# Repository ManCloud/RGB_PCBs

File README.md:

# RGB-PCBs
Console video cable connector PCBs

The user [Arcade TV](https://circuit-board.de/forum/index.php/User/1861-ArcadeTV/) in the Circuit-Board community once created the first ["VSAB"s -> Vertical SCART Adaper Boards](https://circuit-board.de/forum/index.php/Thread/14997-VSAB-Vertical-Scart-Adapter-Boards-outdated/).

In 2020 he found a Post by viletim mentioning, that it's better to have the additional components on console end of the cable instead of the TV end.
So i decided to invent a PCB which would make it easier to solder these cables inspired by the VSABs but for the console end.

As the VSAB boards then no longer needed any components (alsmost) i changed them a bit as well.
 
Links to OSHPark
* Multi-Out:
  * Nintendo: 	https://oshpark.com/shared_projects/a01xTNnj
  * Sony: 		https://oshpark.com/shared_projects/g5j2vvd2
* VSAB
  * Plain: https://oshpark.com/shared_projects/fAsvh5mm
  * 75P: https://oshpark.com/shared_projects/UipCRrXt

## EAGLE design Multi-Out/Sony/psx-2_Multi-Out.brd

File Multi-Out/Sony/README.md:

# Sony
https://oshpark.com/shared_projects/g5j2vvd2

## Purpose
These PCBs can be used to create cables that can be used on Playstation 1,2 and 3.

If you want to use the N64 make sure you have an RGB-modded one or you can only use CV (Composite-Video), as these boards do not support S-Video.

## Configurations
The configuraions all claim to be used with a direct wiring (e.g. with the VSAB-Plain)

### Playstation 1
| Connection | Configuration |
| :-------------: | :-----: |
| SJ2 | either Luma or CV |
| SJ4/C1| 220uF |
| SJ3/C2| 220uF |
| SJ1/C3| 220uF |

### Playstation 2 (3)
| Connection | Configuration |
| :-------------: | :-----: |
| SJ1/C4 | either Luma or CV |
| SJ3/C1| bridged |
| SJ4/C2| bridged |
| SJ5/C3| bridged |

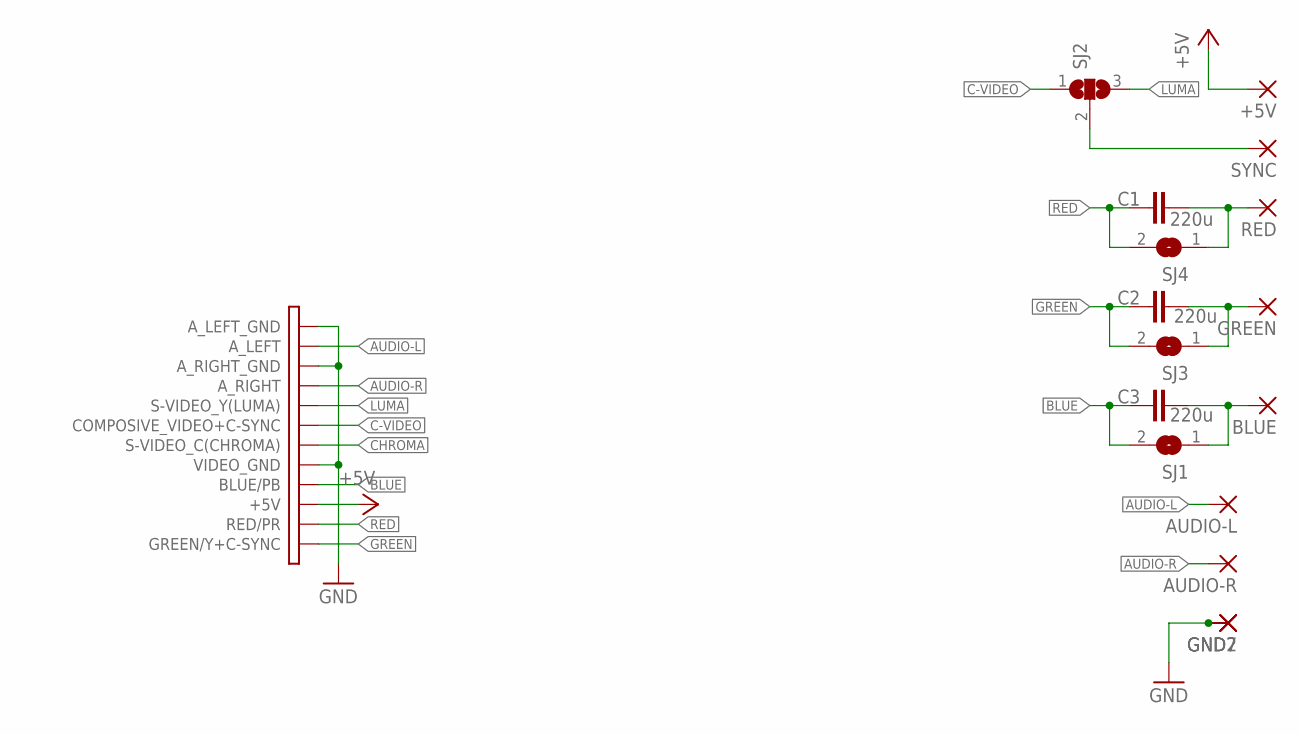
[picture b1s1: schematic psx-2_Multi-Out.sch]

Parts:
+5V: WIREPADSMD1,27-254; SMD1,27-2,54
AUDIO-L: WIREPADSMD1,27-254; SMD1,27-2,54
AUDIO-R: WIREPADSMD1,27-254; SMD1,27-2,54
BLUE: WIREPADSMD1,27-254; SMD1,27-2,54
C1, C2, C3: 220u; C1206
GND2, GND7: WIREPADSMD1,27-254; SMD1,27-2,54
GREEN: WIREPADSMD1,27-254; SMD1,27-2,54
J1: PS/2_MULTI-AV
RED: WIREPADSMD1,27-254; SMD1,27-2,54
SJ1, SJ3, SJ4: SJ
SJ2: SJ2W; SJ_2
SYNC: WIREPADSMD1,27-254; SMD1,27-2,54

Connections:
+5V: +5V.1, J1.+5V
AUDIO-L: AUDIO-L.1, J1.A_LEFT
AUDIO-R: AUDIO-R.1, J1.A_RIGHT
BLUE: C3.1, J1.BLUE/PB, SJ1.2
BLUE'': BLUE.1, C3.2, SJ1.1
C-VIDEO: J1.COMPOSITE_VIDEO+C-S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 (COMPOSIVE_VIDEO+C-SYNC), SJ2.1
CHROMA: J1.S-VIDEO_C(CHROMA)
GND: GND2.1, GND7.1, J1.A_LEFT_GND, J1.A_RIGHT_GND, J1.VIDEO_GND
GREEN: C2.1, J1.GREEN/Y+C-SYNC, SJ3.2
GREEN'': C2.2, GREEN.1, SJ3.1
LUMA: J1.S-VIDEO_Y(LUMA), SJ2.3
RED: C1.1, J1.RED/PR, SJ4.2
RED'': C1.2, RED.1, SJ4.1
SYNC: SJ2.2, SYNC.1

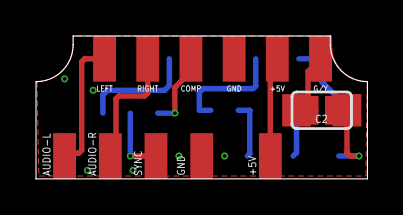
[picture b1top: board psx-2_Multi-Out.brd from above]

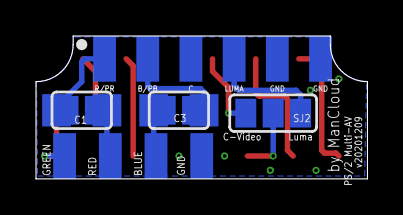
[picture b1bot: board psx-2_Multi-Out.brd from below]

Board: 2 copper layers, 18.4 x 7.9 mm, 17 parts (9 on the bottom side), 13 nets.

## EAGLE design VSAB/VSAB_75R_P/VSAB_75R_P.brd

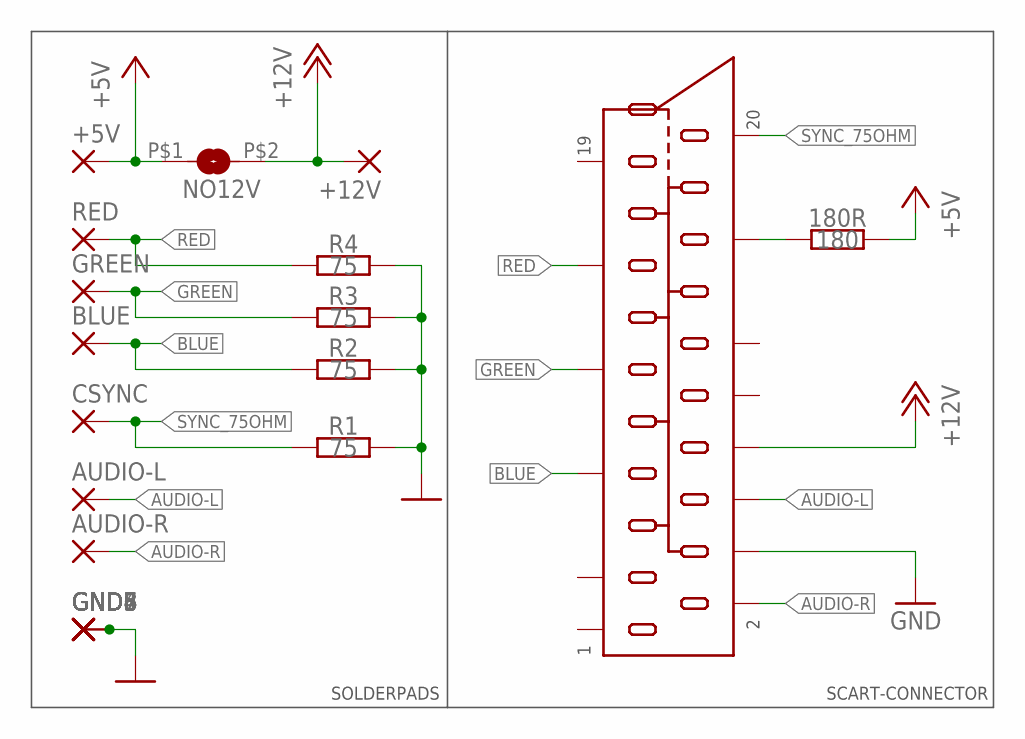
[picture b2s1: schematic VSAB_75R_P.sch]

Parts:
180R: 180; R0805
+5V, +12V: WIREPADSMD5-1,8; 5-1,8
AUDIO-L: WIREPADSMD5-1,8; 5-1,8
AUDIO-R: WIREPADSMD5-1,8; 5-1,8
BLUE: WIREPADSMD5-1,8; 5-1,8
CSYNC: WIREPADSMD5-1,8; 5-1,8
GND, GND3, GND4, GND5, GND6, GND7, GND8: WIREPADSMD5-1,8; 5-1,8
GREEN: WIREPADSMD5-1,8; 5-1,8
NO12V: MY_JUMPER; MYJUMP
R1, R2, R3, R4: 75; R0805
RED: WIREPADSMD5-1,8; 5-1,8
U$2: SCART_PLUG; SCART

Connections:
+5V: 180R.1, +5V.1, NO12V.P$1 (1)
+5V': 180R.2, U$2.16 (AV/RGB_SW)
+12V: +12V.1, NO12V.P$2 (2), U$2.8 (TV/AV_SW)
AUDIO-L: AUDIO-L.1, U$2.6 (AUDIO_IN_L)
AUDIO-R: AUDIO-R.1, U$2.2 (AUDIO_IN_R)
BLUE: BLUE.1, R2.2, U$2.7 (RGB_BLUE/YUV_V/PB)
GND: GND.1, GND3.1, GND4.1, GND5.1, GND6.1, GND7.1, GND8.1, R1.1, R2.1, R3.1, R4.1, U$2.4 (GND), U$2.5 (GND), U$2.9 (GND), U$2.13 (GND), U$2.14 (GND), U$2.17 (GND), U$2.18 (GND)
GREEN: GREEN.1, R3.2, U$2.11 (RGB_GREEN/YUV-Y)
RED: R4.2, RED.1, U$2.15 (RGB_RED/YUV-U/PR/CHROMA)
SYNC_75OHM: CSYNC.1, R1.2, U$2.20 (COMP/SYNC/LUMA_IN)

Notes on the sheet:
SOLDERPADS
SCART-CONNECTOR

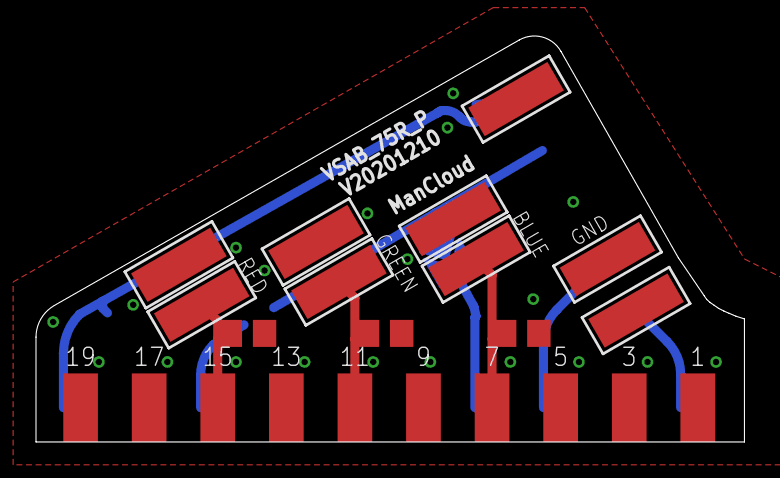
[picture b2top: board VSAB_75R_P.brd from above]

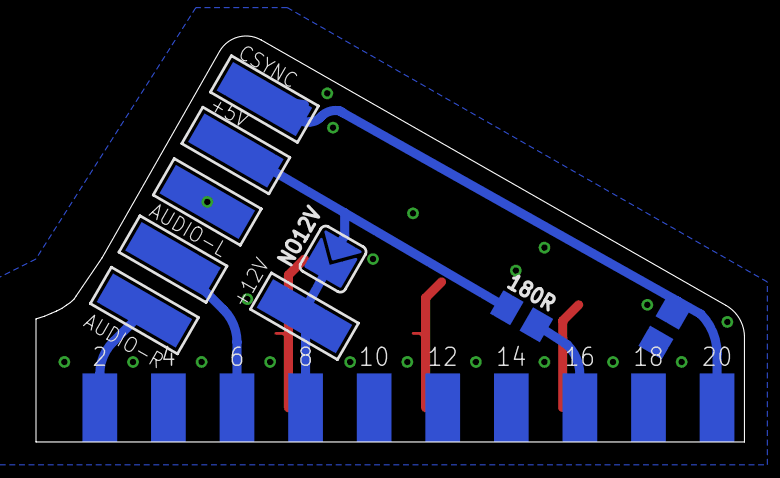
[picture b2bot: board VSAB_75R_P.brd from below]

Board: 2 copper layers, 39.4 x 22.6 mm, 22 parts (9 on the bottom side), 10 nets.

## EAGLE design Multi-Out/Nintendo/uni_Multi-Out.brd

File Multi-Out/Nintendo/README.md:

# Nintendo
https://oshpark.com/shared_projects/a01xTNnj

## Purpose
These PCBs can be used to create cables that can be used on SNES, N64 and GameCube.

If you want to use the N64 make sure you have an RGB-modded one or you can only use CV (Composite-Video), as these boards do not support S-Video.

## Configurations
The configuraions all claim to be used with a direct wiring (e.g. with the VSAB-Plain)

### PAL-SNES
| Connection | Configuration |
| :-------------: | :-----: |
| SJ1/C4 | bridged |
| SJ3/C1| bridged |
| SJ4/C2| bridged |
| SJ5/C3| bridged |
| SJ2| either Luma or CV |
| R1| n.p. |
| R2| 75Ohm |
| R4| 75Ohm |
| R5| 75Ohm |
| R6| 75Ohm |

### NTSC-SNES
| Connection | Configuration |
| :-------------: | :-----: |
| SJ1/C4 | bridged |
| SJ3/C1| 220uF |
| SJ4/C2| 220uF |
| SJ5/C3| 220uF |
| SJ2| either Luma or CV |
| R1| n.p. |
| R2| n.p. |
| R4| n.p. |
| R5| n.p. |
| R6| n.p. |

### PAL-GameCube
| Connection | Configuration |
| :-------------: | :-----: |
| SJ1/C4 | 220uF |
| SJ3/C1| 220uF |
| SJ4/C2| 220uF |
| SJ5/C3| 220uF |
| SJ2| CV |
| R1| n.p. |
| R2| 75Ohm |
| R4| n.p. |
| R5| n.p. |
| R6| n.p. |

### N64
The N64 is different here. It depents on your mod which configuration you need.

E.g.: if you're using [borti4938](https://github.com/borti4938)s [N64Advanced](https://github.com/borti4938/n64rgb/tree/master/advancedRGBmod) Mod, you'd not place any part on the PCB at all:

| Connection | Configuration |
| :-------------: | :-----: |
| SJ1/C4 | bridged |
| SJ3/C1| bridged |
| SJ4/C2| bridged |
| SJ5/C3| bridged |
| SJ2| according to mod |
| R1| n.p. |
| R2| n.p. |
| R4| n.p. |
| R5| n.p. |
| R6| n.p. |

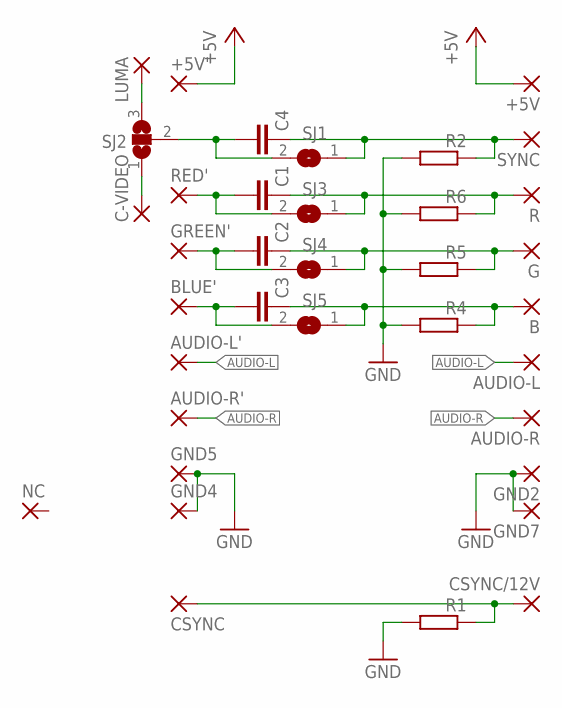
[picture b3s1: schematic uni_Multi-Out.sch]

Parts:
+5V, +5V': WIREPADSMD1,27-254; SMD1,27-2,54
AUDIO-L: WIREPADSMD1,27-254; SMD1,27-2,54
AUDIO-L': WIREPADSMD1,27-254; SMD1,27-2,54
AUDIO-R: WIREPADSMD1,27-254; SMD1,27-2,54
AUDIO-R': WIREPADSMD1,27-254; SMD1,27-2,54
B: WIREPADSMD1,27-254; SMD1,27-2,54
BLUE': WIREPADSMD1,27-254; SMD1,27-2,54
C1, C2, C3, C4: C-EUC1206; C1206
C-VIDEO: WIREPADSMD1,27-254; SMD1,27-2,54
CSYNC: WIREPADSMD1,27-254; SMD1,27-2,54
CSYNC/12V: WIREPADSMD1,27-254; SMD1,27-2,54
G: WIREPADSMD1,27-254; SMD1,27-2,54
GND2, GND4, GND5, GND7: WIREPADSMD1,27-254; SMD1,27-2,54
GREEN': WIREPADSMD1,27-254; SMD1,27-2,54
LUMA: WIREPADSMD1,27-254; SMD1,27-2,54
NC: WIREPADSMD1,27-254; SMD1,27-2,54
R: WIREPADSMD1,27-254; SMD1,27-2,54
R1, R2, R4, R5, R6: R-EU_R0805; R0805
RED': WIREPADSMD1,27-254; SMD1,27-2,54
SJ1, SJ3, SJ4, SJ5: SJ
SJ2: SJ2W; SJ_2
SYNC: WIREPADSMD1,27-254; SMD1,27-2,54

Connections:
+5V: +5V.1, +5V'.1
AUDIO-L: AUDIO-L.1, AUDIO-L'.1
AUDIO-R: AUDIO-R.1, AUDIO-R'.1
BLUE': B.1, C3.1, R4.1, SJ5.1
BLUE'': BLUE'.1, C3.2, SJ5.2
C-VIDEO: C-VIDEO.1, SJ2.1
CSYNC/+12V: CSYNC.1, CSYNC/12V.1, R1.1
GND: GND2.1, GND4.1, GND5.1, GND7.1, R1.2, R2.2, R4.2, R5.2, R6.2
GREEN': C2.1, G.1, R5.1, SJ4.1
GREEN'': C2.2, GREEN'.1, SJ4.2
LUMA: LUMA.1, SJ2.3
unnamed: C4.2, SJ1.2, SJ2.2
RED': C1.1, R.1, R6.1, SJ3.1
RED'': C1.2, RED'.1, SJ3.2
SYNC: C4.1, R2.1, SJ1.1, SYNC.1

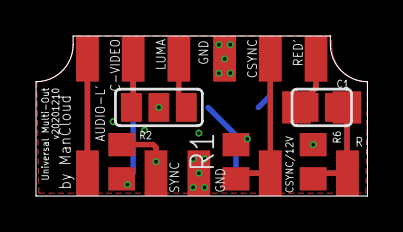
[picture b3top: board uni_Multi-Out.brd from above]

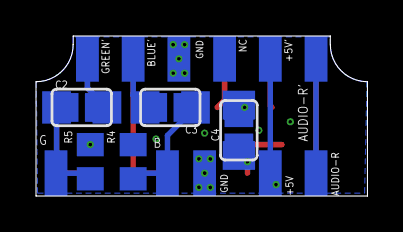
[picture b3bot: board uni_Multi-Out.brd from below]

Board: 2 copper layers, 18.4 x 8.9 mm, 36 parts (19 on the bottom side), 15 nets.

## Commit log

2021-07-02 Inital commit
